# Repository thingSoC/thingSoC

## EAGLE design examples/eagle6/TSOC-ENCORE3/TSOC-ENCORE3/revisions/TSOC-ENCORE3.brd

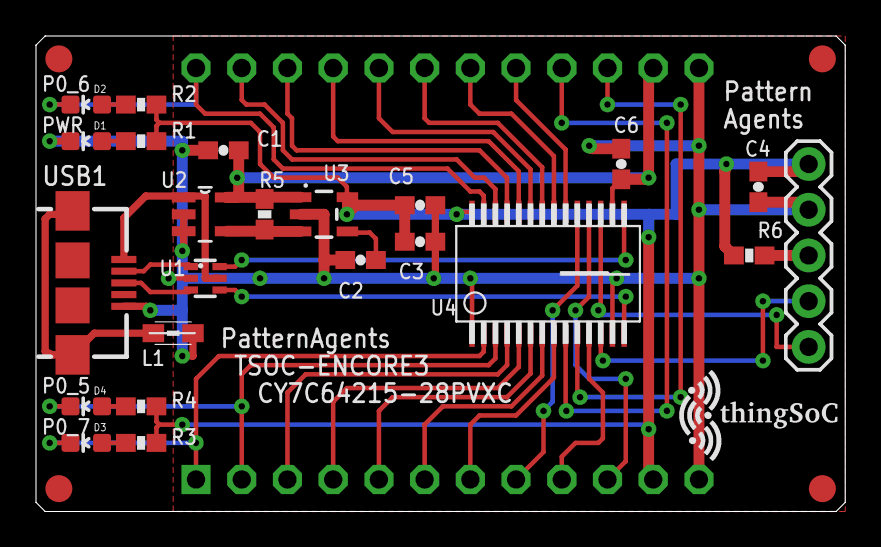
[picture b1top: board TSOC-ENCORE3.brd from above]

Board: 2 copper layers, 45.0 x 26.4 mm, 31 parts (1 on the bottom side), 38 nets.

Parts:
C1, C3: 2.2uF; 0603-CAP
C2: 470pF; 0603-CAP
C4, C5, C6: 0.1uF; 0603-CAP
D1, D2, D3, D4: LED-0603
FID1, FID2, FID3, FID4: FIDUCIAL1.5X3; FIDUCIAL-1.5X3
I2C1: 1X05
L1: MH2029-300Y; 0805
R1, R2, R3, R4: 1K; 0603-RES
R5, R6: 10K; 0603-RES
TSOC: TSOC-24-BB; TSOC-BB-S24
U1: NUF2221W1T2; SOT-363
U2: NCP361SNT1G; SOP95P275X110-5N
U3: MIC5219 3.3V; SOT23-5
U4: CY7C64215-28PVXC; SSOP28
U$1: PA_LOGO_SYMNULL; NULL_SYM
U$2, U$3: TSOC-LOGO-MED
USB1: USB_AB; USB-AB-MICRO-SMD

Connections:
3V3: C3.1, C4.2, C5.2, I2C1.1, R1.1, R2.1, R3.1, R4.1, R6.1, TSOC.11B, U3.5, U4.28
5V0: C1.1, C6.2, R5.2, TSOC.11C, U2.5, U3.1, U4.16
!RST: I2C1.3, R6.2
!USB_FAULT: R5.1, U2.4, U3.3
BLUE: D3.A, R3.2
BYPASS: C2.1, U3.4
GND: C1.2, C2.2, C3.2, C4.1, C5.1, C6.1, D1.C, I2C1.2, L1.2, TSOC.12B, TSOC.12C, U1.2, U2.2, U2.3, U3.2, U4.1, U4.13, USB1.GND
GRN: D1.A, R1.2
P0_0: TSOC.4C, U4.24
P0_1: TSOC.4B, U4.5
P0_2: TSOC.3C, U4.25
P0_3: TSOC.3B, U4.4
P0_4: TSOC.2C, U4.26
P0_5: D4.C, TSOC.2B, U4.3
P0_6: D2.C, TSOC.1C, U4.27
P0_7: D3.C, TSOC.1B, U4.2
P1_0: I2C1.5, U4.17
P1_1: I2C1.4, U4.12
P1_2: TSOC.10B, U4.18
P1_3: TSOC.9B, U4.11
P1_4: TSOC.8B, U4.19
P1_5: TSOC.10C, U4.10
P1_6: TSOC.8C, U4.20
P1_7: TSOC.9C, U4.9
P2_0: TSOC.7C, U4.21
P2_1: TSOC.7B, U4.8
P2_2: TSOC.6C, U4.22
P2_3: TSOC.6B, U4.7
P2_4: TSOC.5C, U4.23
P2_5: TSOC.5B, U4.6
RED: D2.A, R2.2
USB1_DM: U1.1, USB1.D-
USB1_DP: U1.3, USB1.D+
USB1_M: U1.6, U4.15
USB1_P: U1.4, U4.14
USB1_SHIELD: L1.1, USB1.SHIELD1, USB1.SHIELD2
USB1_VBUS: U1.5, U2.1, USB1.VBUS
YEL: D4.A, R4.2

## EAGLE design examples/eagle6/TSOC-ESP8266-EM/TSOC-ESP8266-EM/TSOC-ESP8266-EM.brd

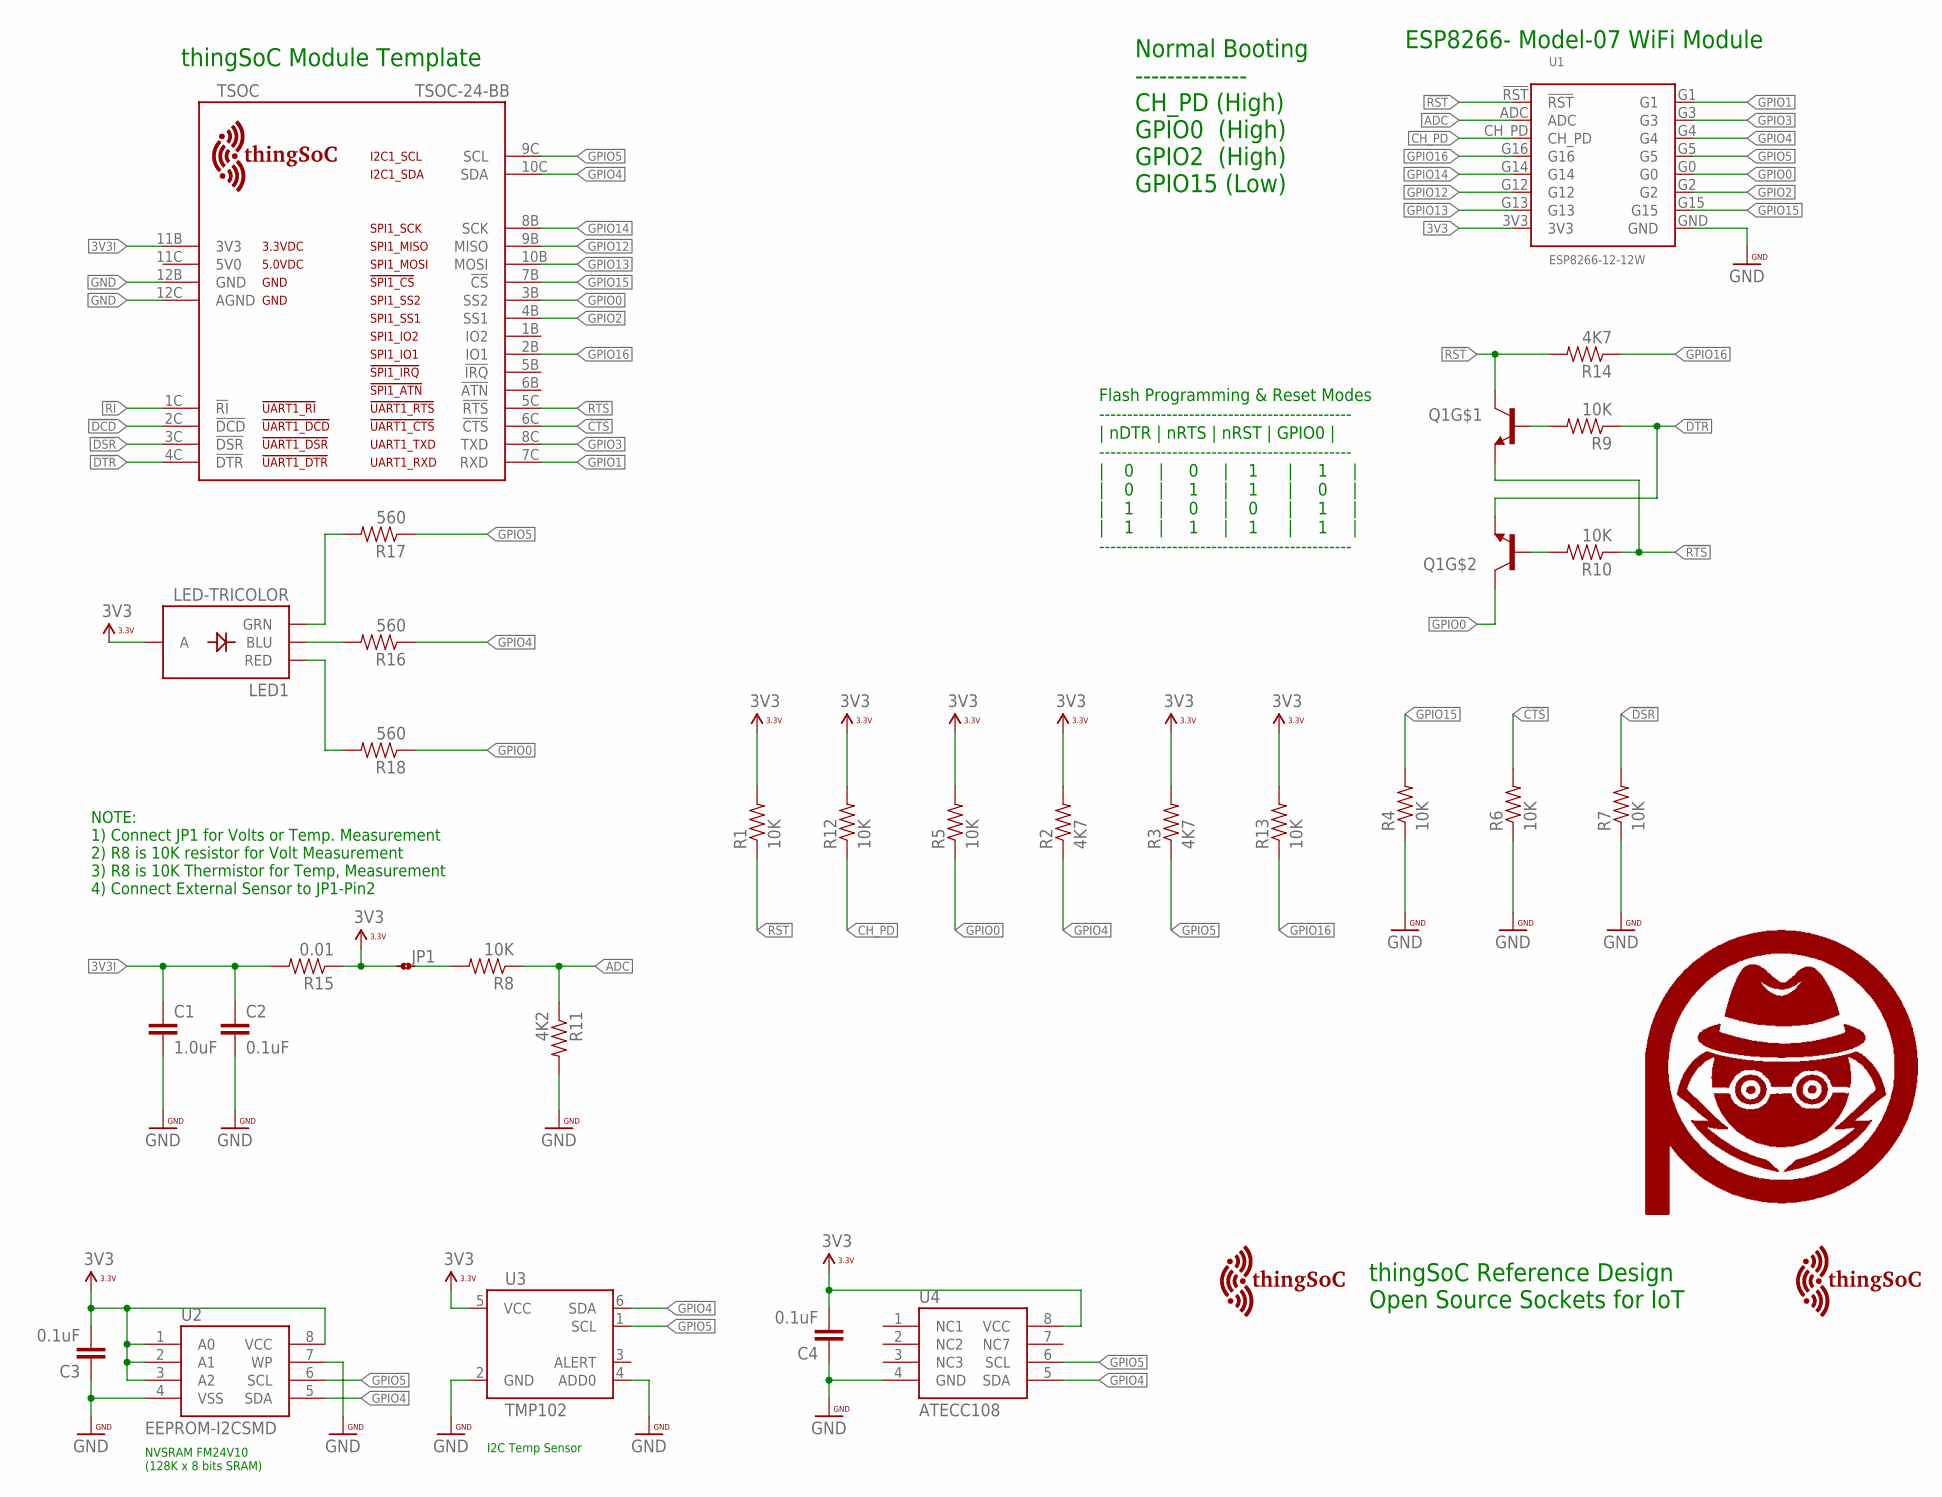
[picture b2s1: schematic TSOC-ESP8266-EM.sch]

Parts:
C1: 1.0uF; 0402-CAP
C2, C3, C4: 0.1uF; 0402-CAP
JP1: JMP-2-NO-0402
LED1: LED-TRICOLOR; LED-TRICOLOR-SMD
Q1: MMBT2222A; SOT363
R1, R4, R5, R6, R7, R8, R9, R10, R12, R13: 10K; 0402-RES
R2, R3, R14: 4K7; 0402-RES
R11: 4K2; 0402-RES
R15: 0.01; 0402-RES
R16, R17, R18: 560; 0402-RES
TSOC: TSOC-24-BB; TSOC-BB-S24
U1: ESP8266-12-12W; ESP8266-12W
U2: EEPROM-I2CSMD; SO08
U3: TMP102; SOT563
U4: ATECC108; SOIC8
U$11: PA_LOGO_SYMMED; PA_LOGO_AGENT_MED_SYM
U$19, U$20: TSOC-LOGO-MED

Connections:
3V3: C3.2, C4.2, JP1.1, LED1.A, R1.2, R2.2, R3.2, R5.2, R12.2, R13.2, R15.1, U1.3V3, U2.1 (A0), U2.2 (A1), U2.3 (A2), U2.8 (VCC), U3.5 (VCC), U4.8 (VCC)
3V3I: C1.1, C2.1, R15.2, TSOC.11B (3V3)
!CTS: R6.2, TSOC.6C (!CTS)
!DCD: TSOC.2C (!DCD)
!DSR: R7.2, TSOC.3C (!DSR)
!DTR: Q1.1 (E), R9.1, TSOC.4C (!DTR)
!RI: TSOC.1C (!RI)
!RST: Q1.3 (C), R1.1, R14.2, U1.!RST
!RTS: Q1.4 (E), R10.1, TSOC.5C (!RTS)
ADC: R8.1, R11.1, U1.ADC
ADC_RAW: JP1.2, R8.2
BLU: LED1.B (BLU), R16.2
CH_PD: R12.1, U1.CH_PD
GND: C1.2, C2.2, C3.1, C4.1, R4.1, R6.1, R7.1, R11.2, TSOC.12B (GND), TSOC.12C (AGND), U1.GND, U2.4 (VSS), U2.7 (WP), U3.2 (GND), U3.4 (ADD0), U4.4 (GND)
GPIO0: Q1.6 (C), R5.1, R18.1, TSOC.3B (SS2), U1.G0
GPIO1: TSOC.7C (RXD), U1.G1
GPIO2: TSOC.4B (SS1), U1.G2
GPIO3: TSOC.8C (TXD), U1.G3
GPIO4: R2.1, R16.1, TSOC.10C (SDA), U1.G4, U2.5 (SDA), U3.6 (SDA), U4.5 (SDA)
GPIO5: R3.1, R17.1, TSOC.9C (SCL), U1.G5, U2.6 (SCL), U3.1 (SCL), U4.6 (SCL)
GPIO12: TSOC.9B (MISO), U1.G12
GPIO13: TSOC.10B (MOSI), U1.G13
GPIO14: TSOC.8B (SCK), U1.G14
GPIO15: R4.2, TSOC.7B (!CS), U1.G15
GPIO16: R13.1, R14.1, TSOC.2B (IO1), U1.G16
GRN: LED1.G (GRN), R17.2
unnamed: Q1.5 (B), R9.2
unnamed: Q1.2 (B), R10.2
RED: LED1.R (RED), R18.2

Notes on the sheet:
thingSoC Reference Design Open Source Sockets for IoT
thingSoC Module Template
Normal Booting -------------- CH_PD (High) GPIO0 (High) GPIO2 (High) GPIO15 (Low)
ESP8266- Model-07 WiFi Module
Flash Programming & Reset Modes --------------------------------------------- | nDTR | nRTS | nRST | GPIO0 | --------------------------------------------- | 0 | 0 | 1 | 1 | | 0 | 1 | 1 | 0 | | 1 | 0 | 0 | 1 | | 1 | 1 | 1 | 1 | ---------------------------------------------
NOTE: 1) Connect JP1 for Volts or Temp. Measurement 2) R8 is 10K resistor for Volt Measurement 3) R8 is 10K Thermistor for Temp, Measurement 4) Connect External Sensor to JP1-Pin2
NVSRAM FM24V10 (128K x 8 bits SRAM)
I2C Temp Sensor

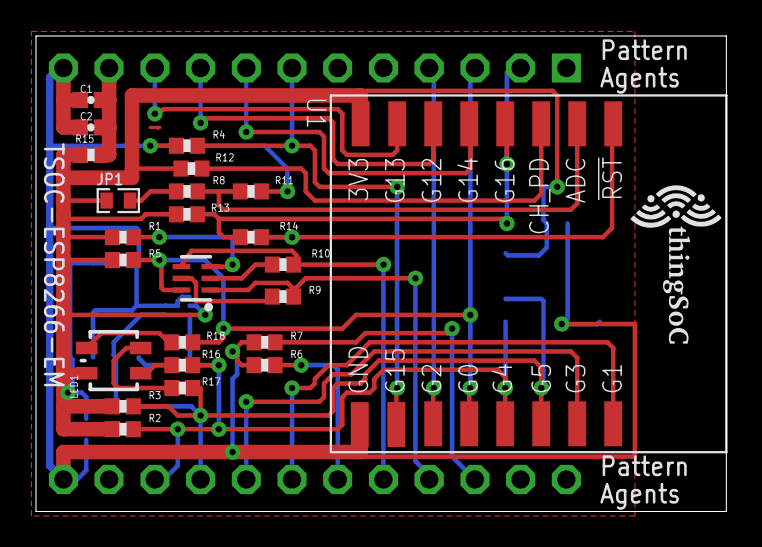
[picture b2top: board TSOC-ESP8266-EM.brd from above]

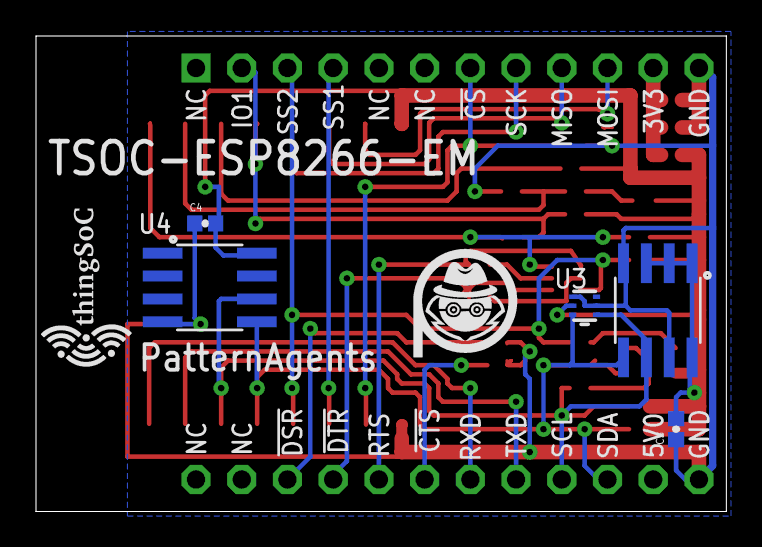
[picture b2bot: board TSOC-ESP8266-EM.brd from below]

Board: 2 copper layers, 38.4 x 26.4 mm, 33 parts (7 on the bottom side), 27 nets.

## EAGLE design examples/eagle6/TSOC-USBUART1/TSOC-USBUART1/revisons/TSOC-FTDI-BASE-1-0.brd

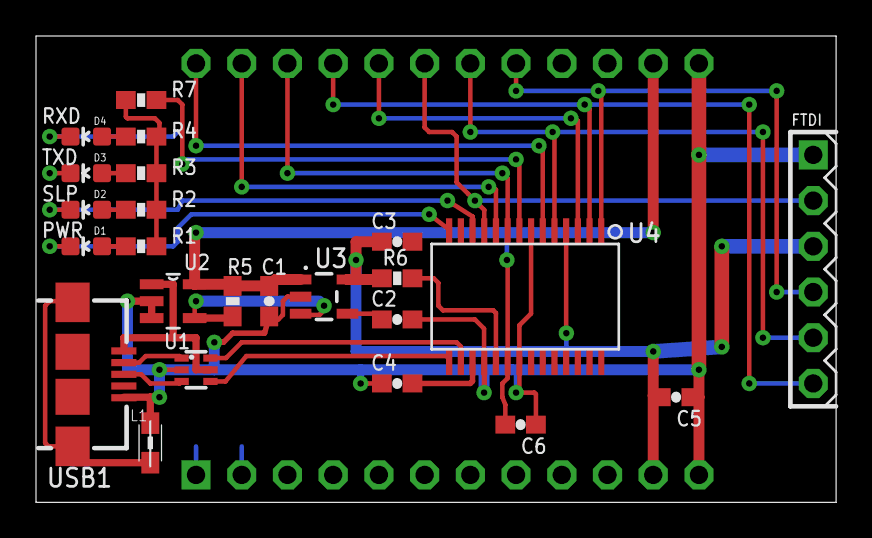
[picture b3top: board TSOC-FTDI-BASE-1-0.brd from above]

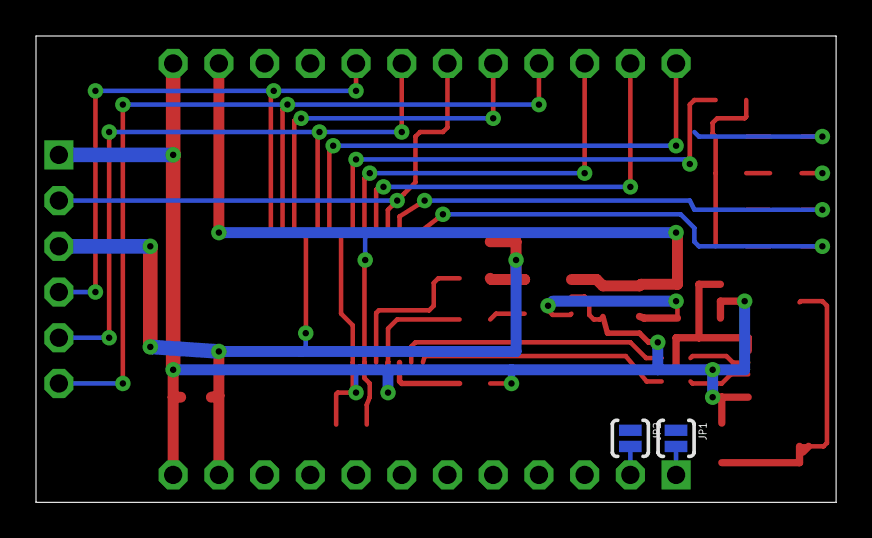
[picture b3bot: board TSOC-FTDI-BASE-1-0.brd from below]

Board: 2 copper layers, 44.5 x 25.9 mm, 27 parts (2 on the bottom side), 33 nets.

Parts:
C1, C3: 2.2uF; 0603-CAP
C2: 470pF; 0603-CAP
C4: 1.0uF; 0603-CAP
C5, C6: 0.1uF; 0603-CAP
D1, D2, D3, D4: LED-0603
FTDI: PA_FTDI_BASIC_HOST-; PA_FTDI_M5X1
JP1, JP2: JMP-2-NO
L1: MH2029-300Y; 0805
R1, R2, R3, R4: 1K; 0603-RES
R5, R6, R7: 10K; 0603-RES
TSOC: TSOC-24-BB; TSOC-BB-S24
U1: NUF2221W1T2; SOT-363
U2: NCP361SNT1G; SOP95P275X110-5N
U3: MIC5219 3.3V; SOT23-5
U4: CY7C65213-28PVXI; SSOP28DB
USB1: USB_AB; USB-AB-MICRO-SMD

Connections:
3V3: C3.1, C5.2, FTDI.3, R1.1, R2.1, R3.1, R4.1, R6.1, R7.1, TSOC.11B, U3.5, U4.4
5V0: C1.1, C6.2, R5.2, TSOC.11C, U2.5, U3.1, U4.20
!CTS: FTDI.2, TSOC.6C, U4.11
!DCD: TSOC.2C, U4.10
!DSR: TSOC.3C, U4.9
!DTR: FTDI.6, TSOC.4C, U4.2
!POWER: D1.C, U4.14
!RI: TSOC.1C, U4.6
!RST: R6.2, U4.19
!RTS: TSOC.5C, U4.3
!RX_LED: D4.C, U4.22
!SLEEP: D2.C, JP1.1, U4.12
!TX_LED: D3.C, U4.23
!USB_FAULT: R5.1, U2.4, U3.3
BLUE: D3.A, R3.2
BUS_DET: R7.2, U4.8
BYPASS: C2.1, U3.4
GND: C1.2, C2.2, C3.2, C4.1, C5.1, C6.1, FTDI.1, L1.2, TSOC.12B, TSOC.12C, U1.2, U2.2, U2.3, U3.2, U4.7, U4.18, U4.21, USB1.GND
GRN: D1.A, R1.2
IO1: JP2.2, TSOC.2B
IO2: JP1.2, TSOC.1B
RED: D2.A, R2.2
RXD: FTDI.5, TSOC.7C, U4.5
TXD: FTDI.4, TSOC.8C, U4.1
TXDEN: JP2.1, U4.13
USB1_DM: U1.1, USB1.D-
USB1_DP: U1.3, USB1.D+
USB1_M: U1.6, U4.16
USB1_P: U1.4, U4.15
USB1_SHIELD: L1.1, USB1.SHIELD1, USB1.SHIELD2
USB1_VBUS: U1.5, U2.1, USB1.VBUS
VCCD: C4.2, U4.17
YEL: D4.A, R4.2

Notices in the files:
parts and their libraries:
thingSoC: License : http://creativecommons.org/licenses/by-sa/4.0
(Creative Commons 4.0)
SparkFun-PowerIC: Licensing: Creative Commons ShareAlike 4.0 International - https://creativecommons.org/licenses/by-sa/4.0
PatternAgents-Logos: License : http://creativecommons.org/licenses/by-sa/3.0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
